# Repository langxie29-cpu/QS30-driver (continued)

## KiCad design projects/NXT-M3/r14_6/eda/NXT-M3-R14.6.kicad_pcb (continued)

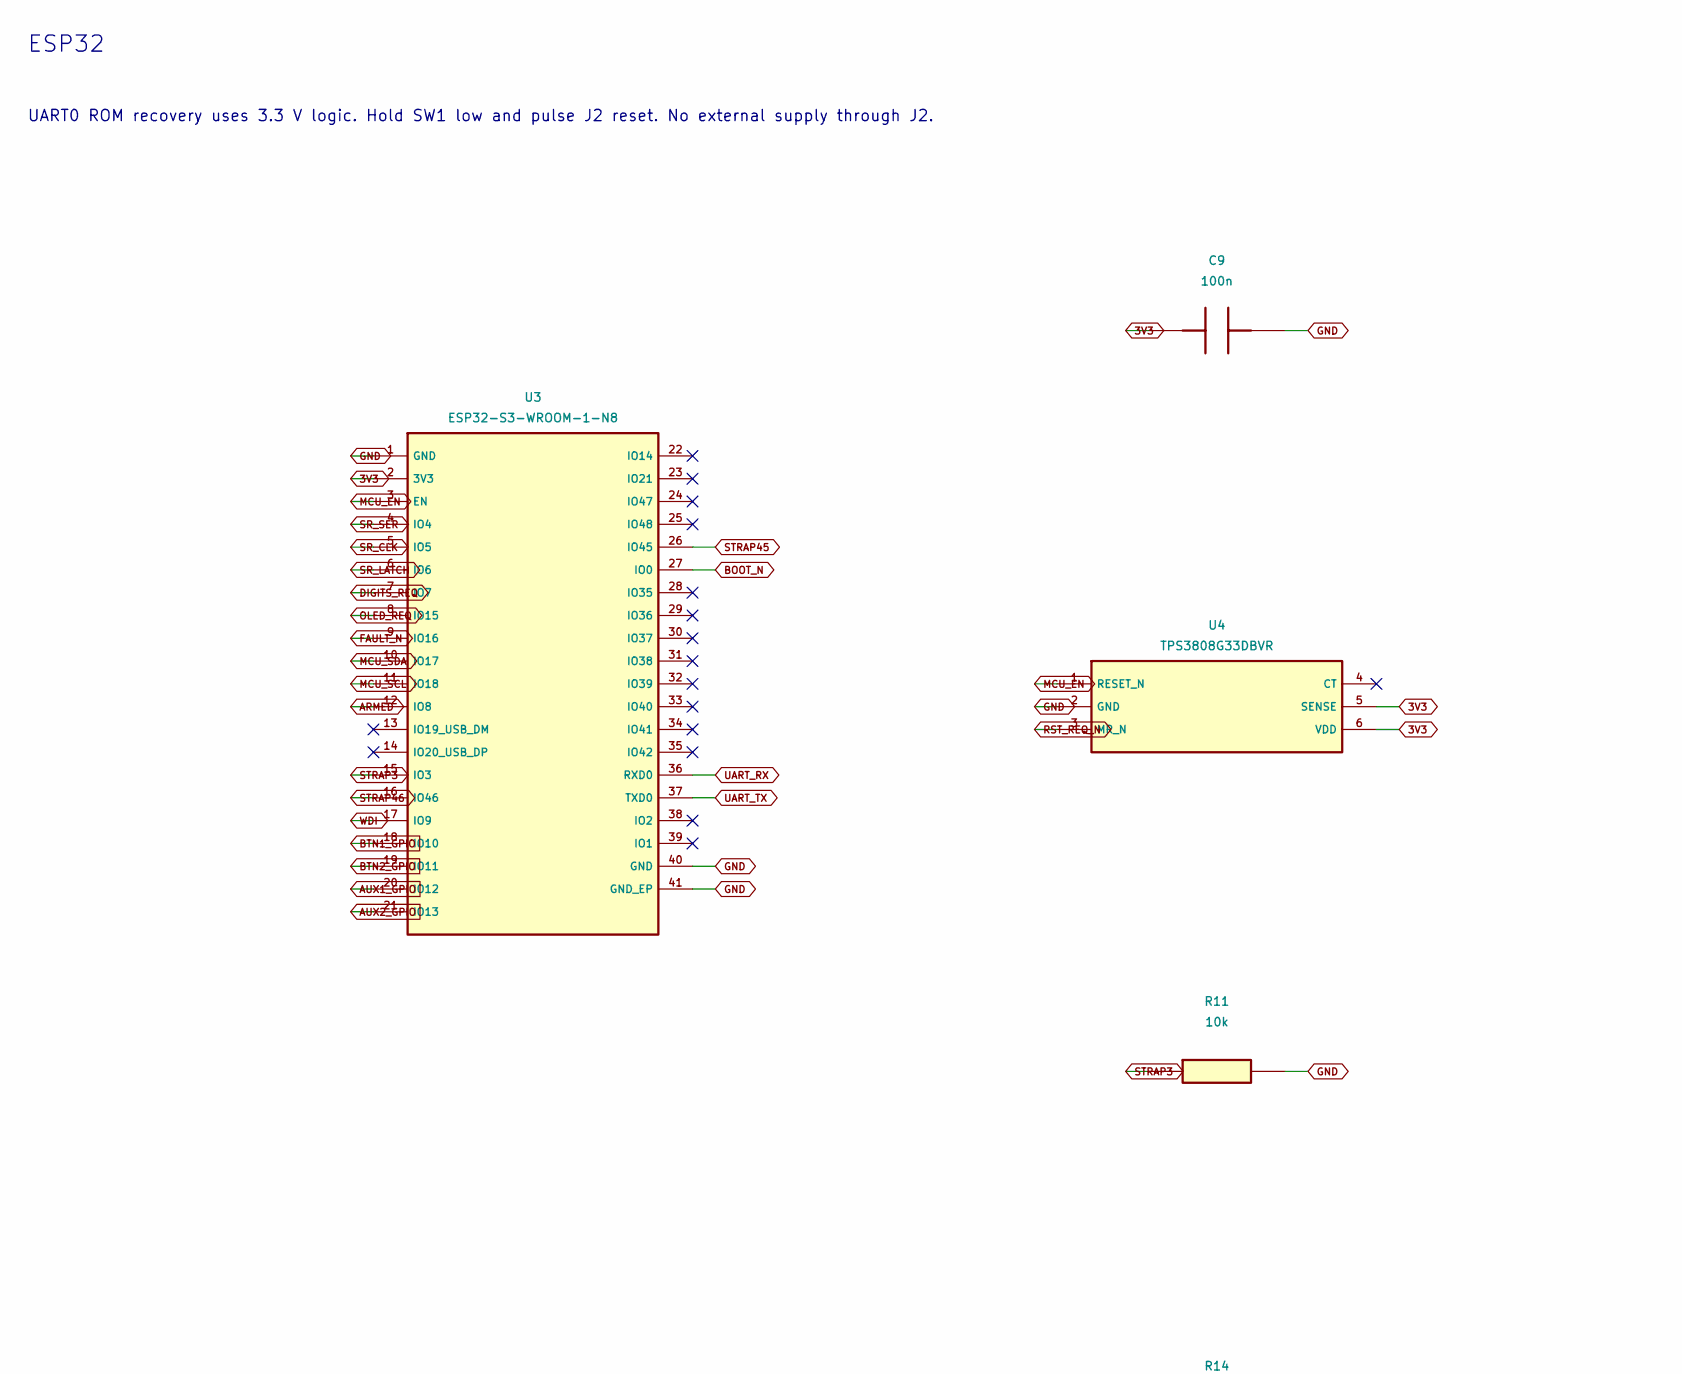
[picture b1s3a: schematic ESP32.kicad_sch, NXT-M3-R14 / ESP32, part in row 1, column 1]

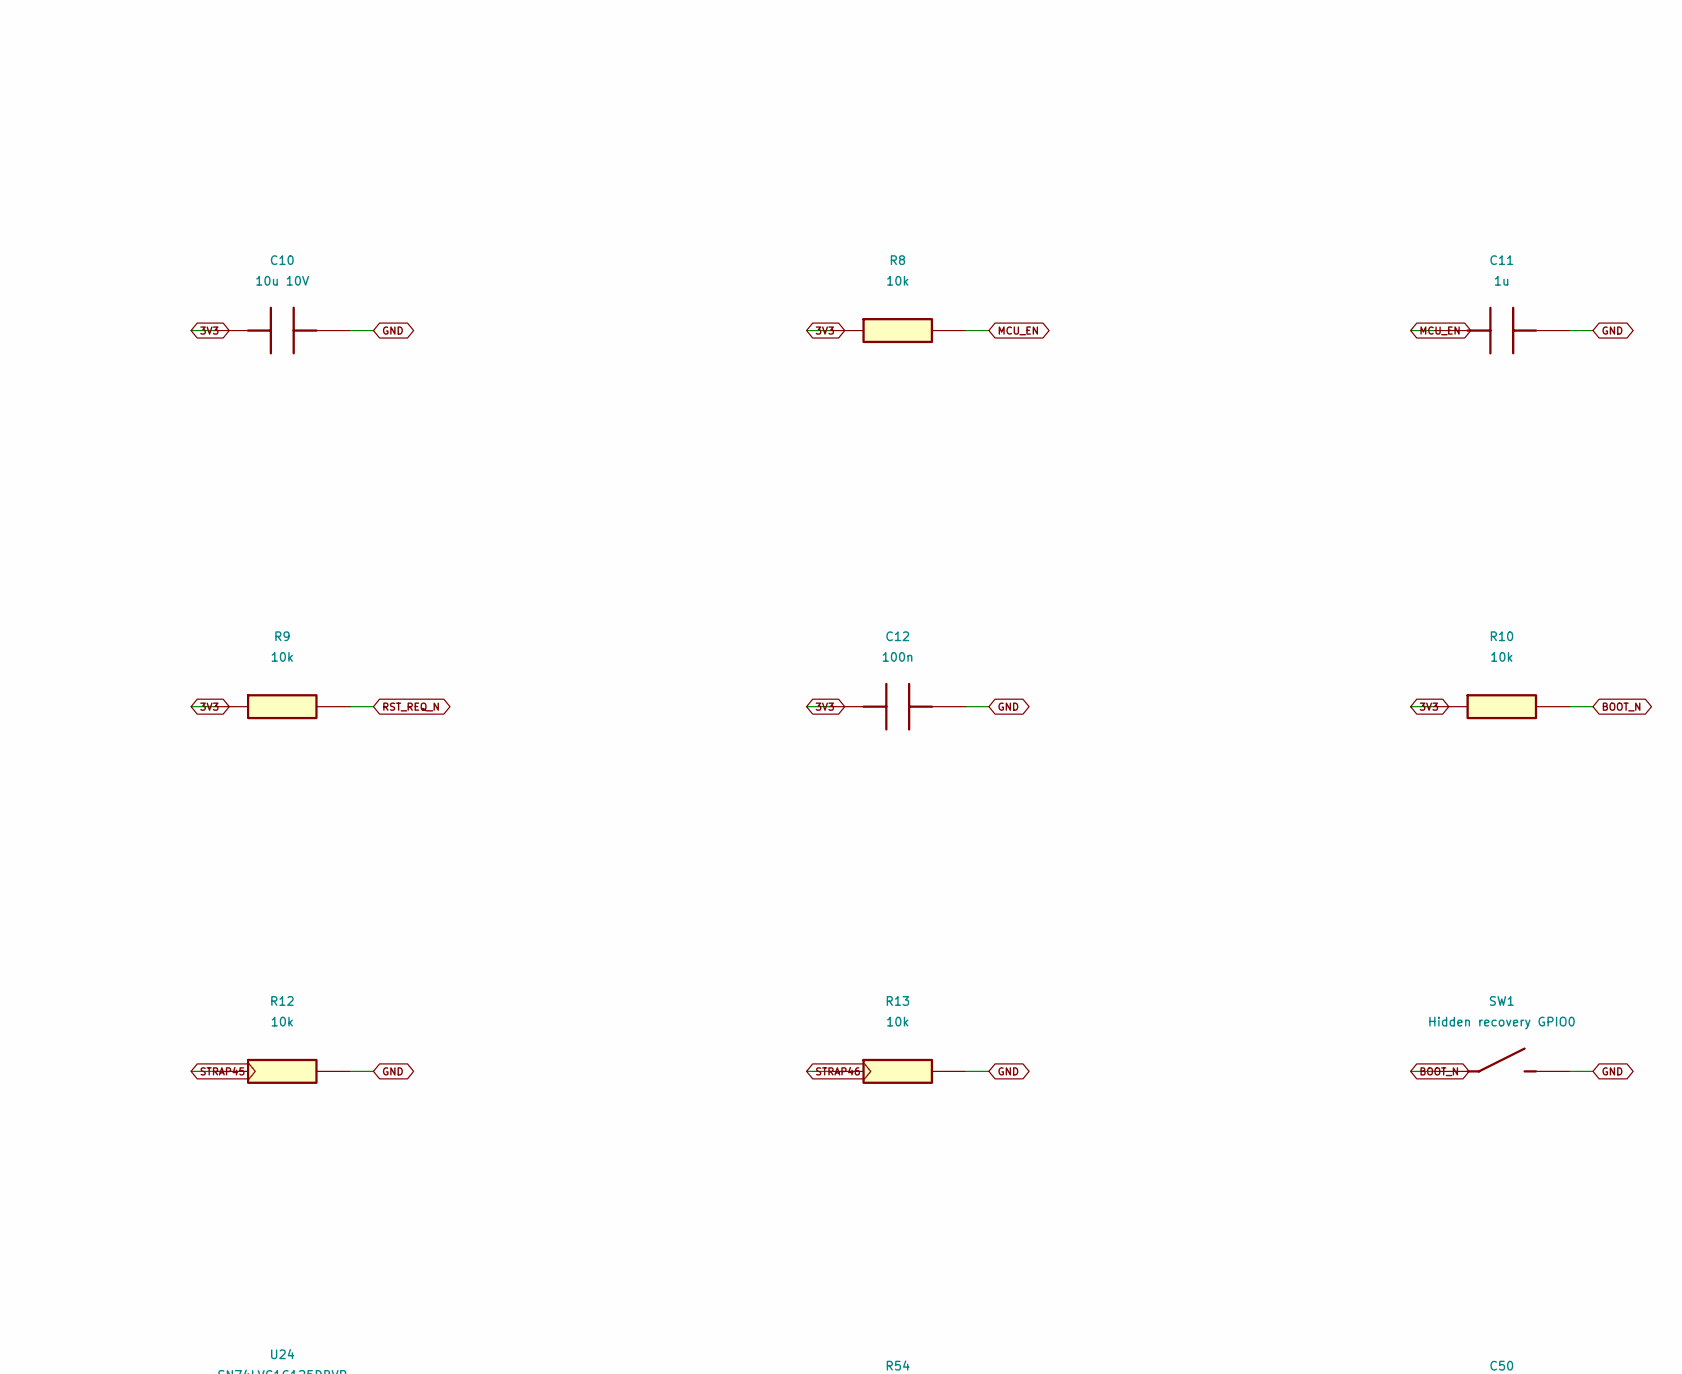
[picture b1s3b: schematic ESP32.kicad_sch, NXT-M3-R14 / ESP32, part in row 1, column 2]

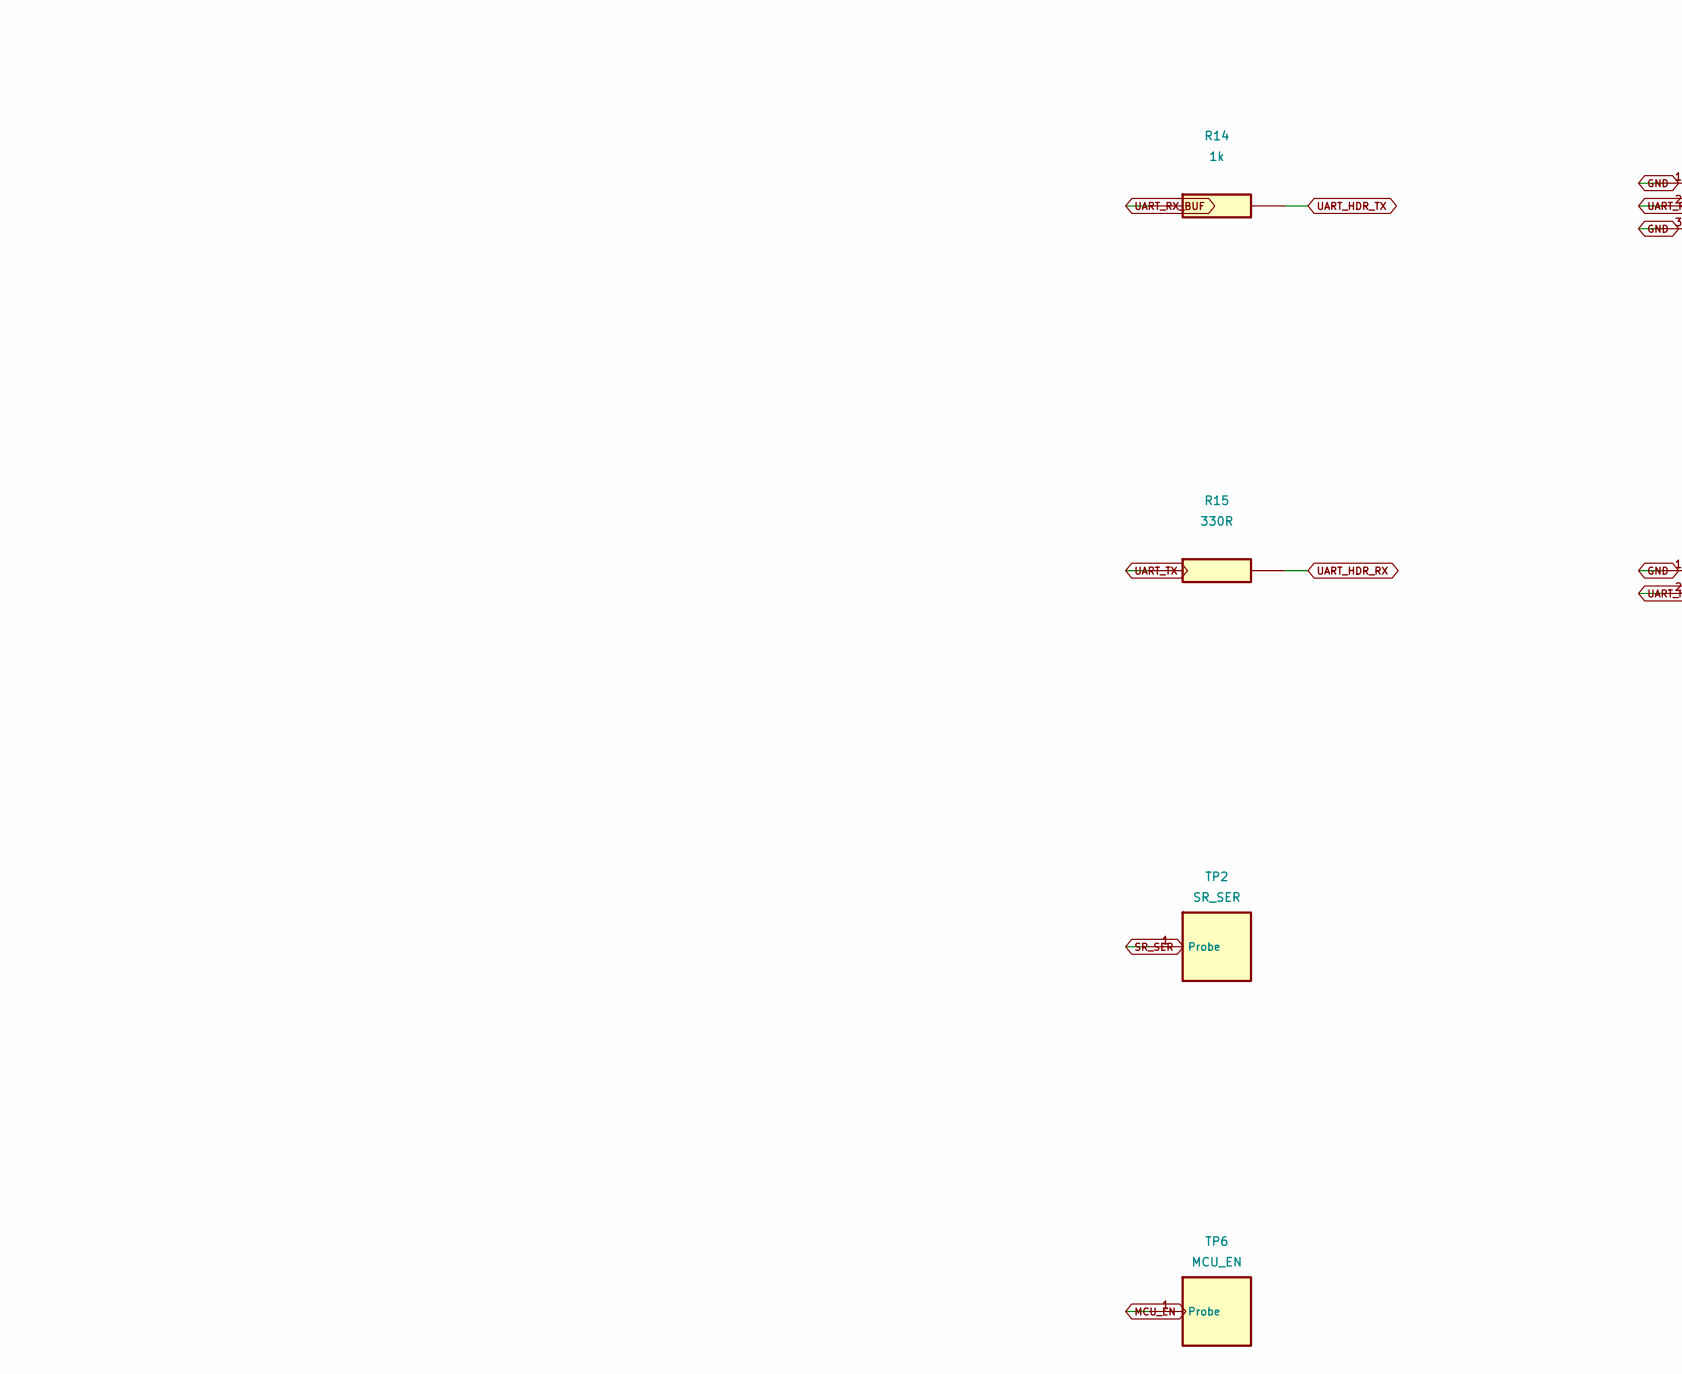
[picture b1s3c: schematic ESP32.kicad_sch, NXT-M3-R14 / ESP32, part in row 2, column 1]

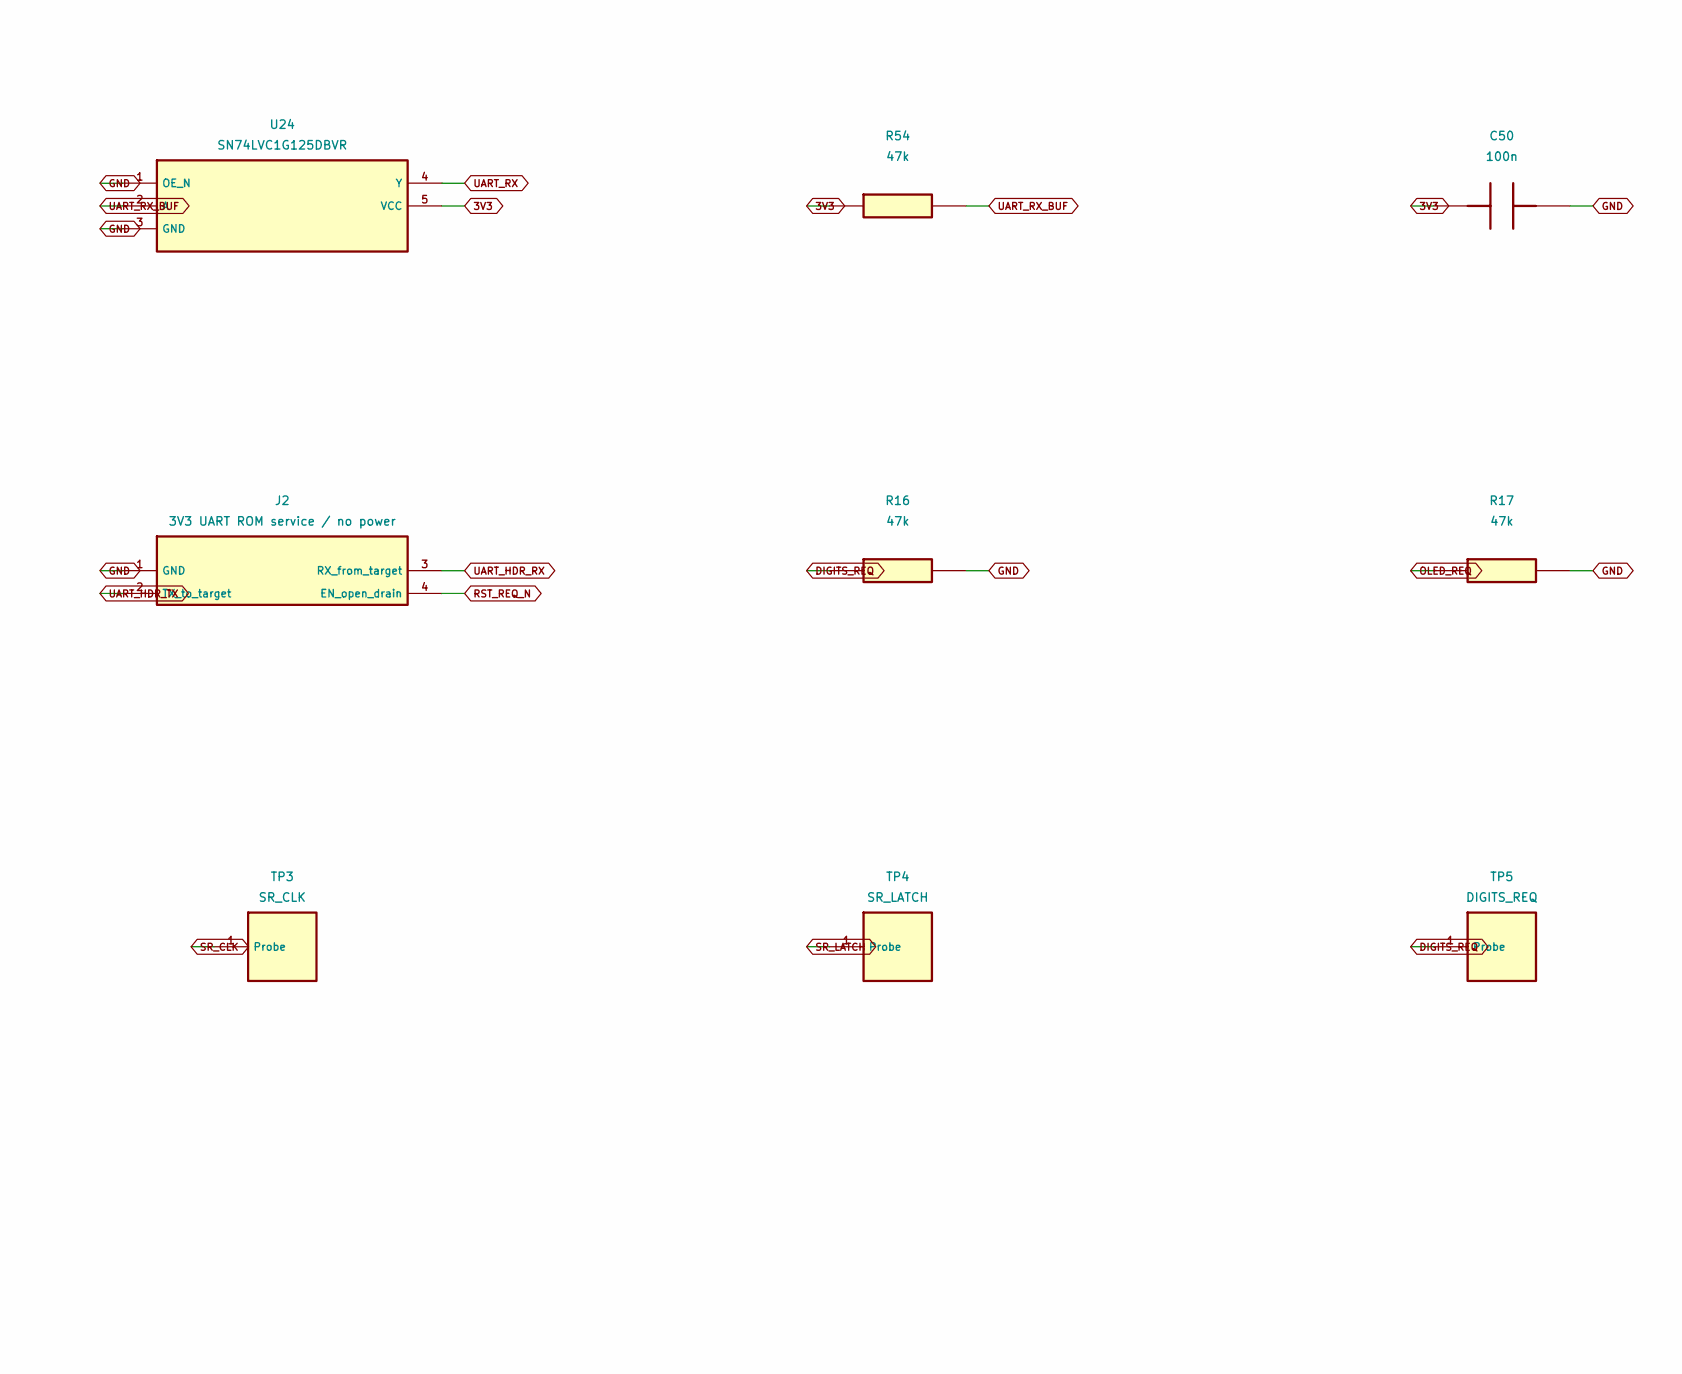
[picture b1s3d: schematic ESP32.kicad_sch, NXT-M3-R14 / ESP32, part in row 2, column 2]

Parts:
C9, C12, C50: 100n; C_0603_1608Metric
C10: 10u 10V; C_0805_2012Metric
C11: 1u; C_0603_1608Metric
J2: 3V3 UART ROM service / no power; PinHeader_1x04_P2.54mm_Vertical
R8, R9, R10, R11, R12, R13: 10k; R_0603_1608Metric
R14: 1k; R_0603_1608Metric
R15: 330R; R_0603_1608Metric
R16, R17, R54: 47k; R_0603_1608Metric
SW1: Hidden recovery GPIO0; SW_SPST_TL3342; MPN TL3342F160QG
TP2: SR_SER; TestPoint_Pad_D1.5mm
TP3: SR_CLK; TestPoint_Pad_D1.5mm
TP4: SR_LATCH; TestPoint_Pad_D1.5mm
TP5: DIGITS_REQ; TestPoint_Pad_D1.5mm
TP6: MCU_EN; TestPoint_Pad_D1.5mm
U3: ESP32-S3-WROOM-1-N8; ESP32-S3-WROOM-1_0.30mm_Drill; MPN ESP32-S3-WROOM-1-N8
U4: TPS3808G33DBVR; SOT-23-6; MPN TPS3808G33DBVR
U24: SN74LVC1G125DBVR; SOT-23-5; MPN SN74LVC1G125DBVR

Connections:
3V3: C9.1, C10.1, C12.1, C50.1, R8.1, R9.1, R10.1, R54.1, U3.2 (3V3), U4.5 (SENSE), U4.6 (VDD), U24.5 (VCC); also elsewhere on the board
ARMED: U3.12 (IO8); also elsewhere on the board
AUX1_GPIO: U3.20 (IO12); also elsewhere on the board
AUX2_GPIO: U3.21 (IO13); also elsewhere on the board
BOOT_N: R10.2, SW1.1, U3.27 (IO0)
BTN1_GPIO: U3.18 (IO10); also elsewhere on the board
BTN2_GPIO: U3.19 (IO11); also elsewhere on the board
DIGITS_REQ: R16.1, TP5.1, U3.7 (IO7); also elsewhere on the board
FAULT_N: U3.9 (IO16); also elsewhere on the board
GND: C9.2, C10.2, C11.2, C12.2, C50.2, J2.1 (GND), R11.2, R12.2, R13.2, R16.2, R17.2, SW1.2, U3.1 (GND), U3.40 (GND), U3.41 (GND_EP), U4.2 (GND), U24.1 (OE_N), U24.3 (GND); also elsewhere on the board
MCU_EN: C11.1, R8.2, TP6.1, U3.3 (EN), U4.1 (RESET_N); also elsewhere on the board
MCU_SCL: U3.11 (IO18); also elsewhere on the board
MCU_SDA: U3.10 (IO17); also elsewhere on the board
OLED_REQ: R17.1, U3.8 (IO15); also elsewhere on the board
RST_REQ_N: J2.4 (EN_open_drain), R9.2, U4.3 (MR_N)
SR_CLK: TP3.1, U3.5 (IO5); also elsewhere on the board
SR_LATCH: TP4.1, U3.6 (IO6); also elsewhere on the board
SR_SER: TP2.1, U3.4 (IO4); also elsewhere on the board
STRAP3: R11.1, U3.15 (IO3)
STRAP45: R12.1, U3.26 (IO45)
STRAP46: R13.1, U3.16 (IO46)
UART_HDR_RX: J2.3 (RX_from_target), R15.2
UART_HDR_TX: J2.2 (TX_to_target), R14.2
UART_RX: U3.36 (RXD0), U24.4 (Y)
UART_RX_BUF: R14.1, R54.2, U24.2 (A)
UART_TX: R15.1, U3.37 (TXD0)
WDI: U3.17 (IO9); also elsewhere on the board

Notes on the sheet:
ESP32
UART0 ROM recovery uses 3.3 V logic. Hold SW1 low and pulse J2 reset. No external supply through J2.

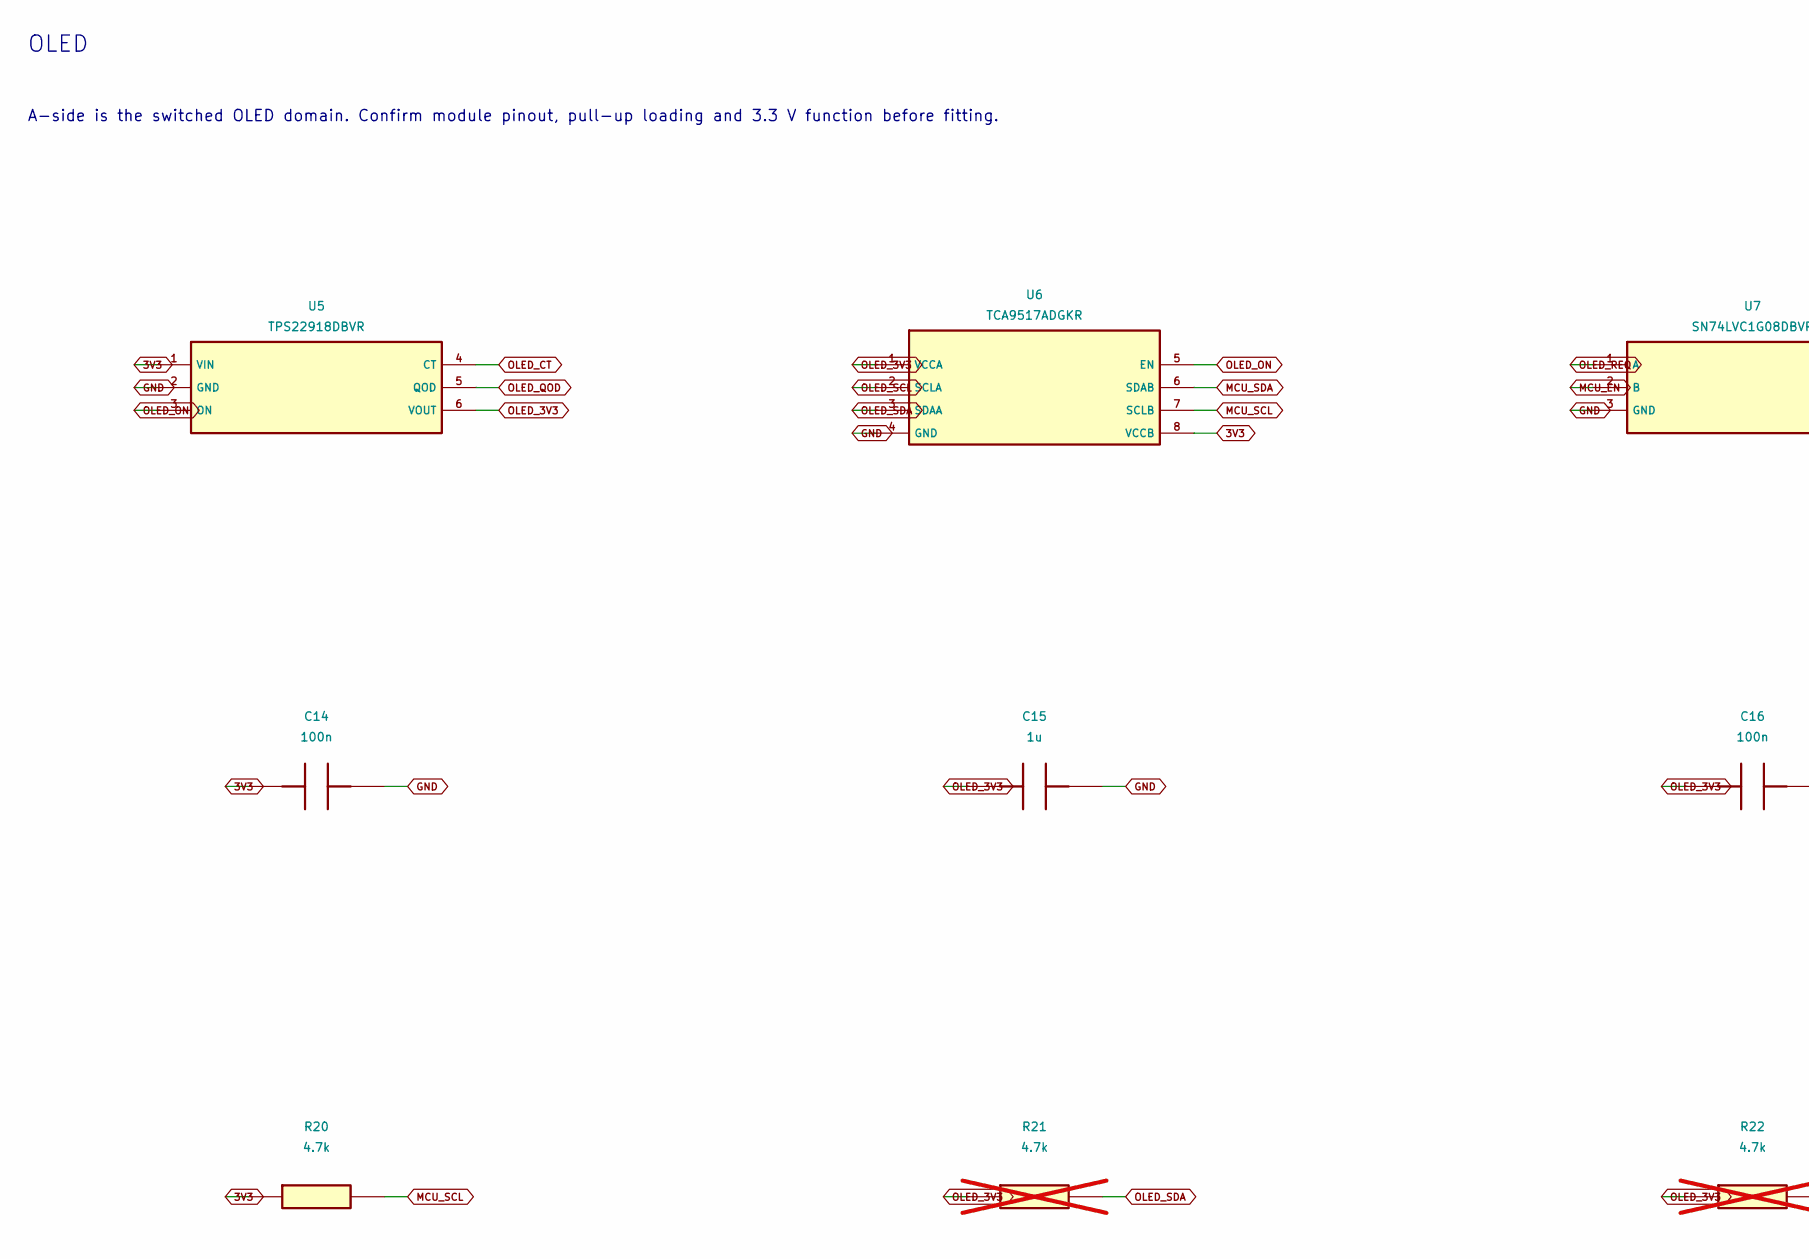
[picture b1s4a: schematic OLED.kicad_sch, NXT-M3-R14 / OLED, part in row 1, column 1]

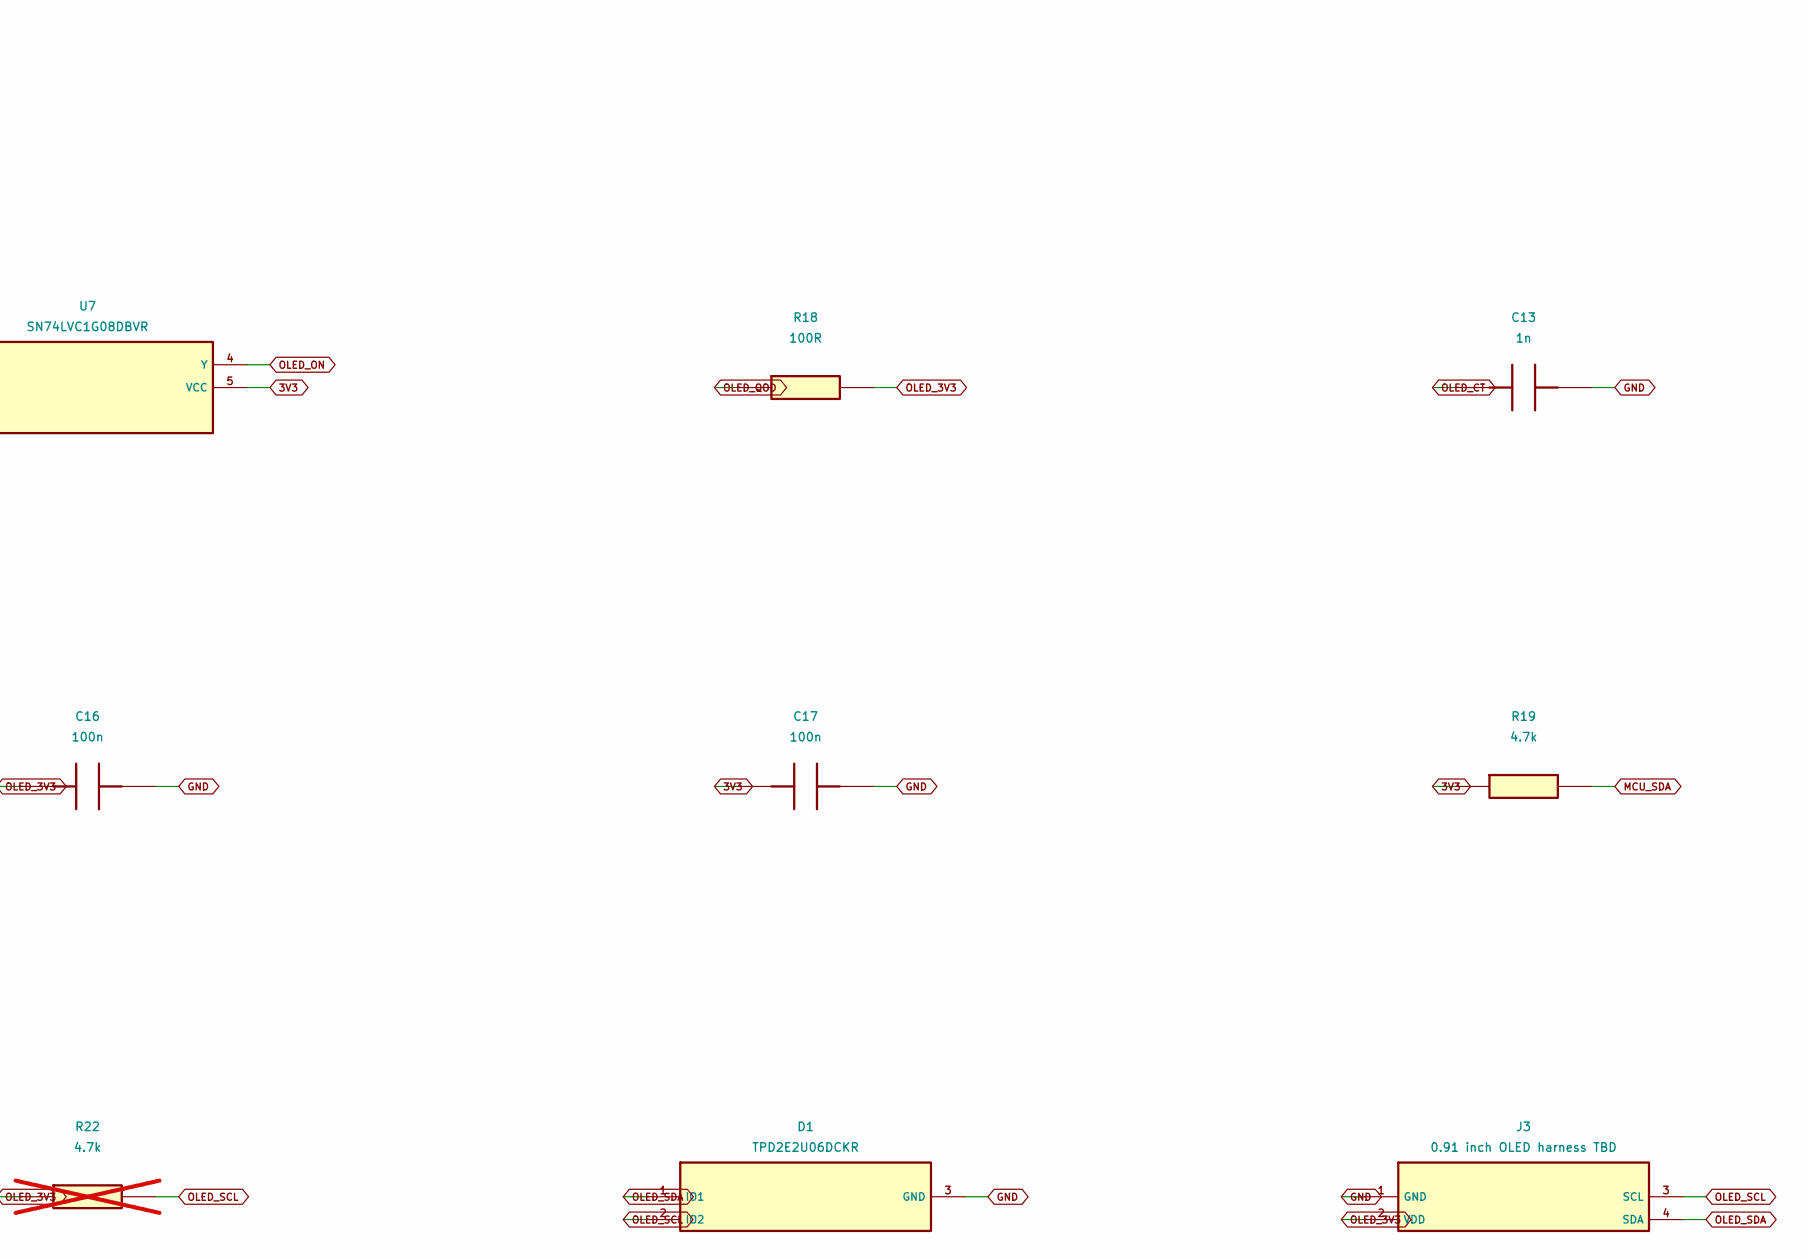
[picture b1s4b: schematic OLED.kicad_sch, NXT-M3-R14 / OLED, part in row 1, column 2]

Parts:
C13: 1n; C_0603_1608Metric
C14, C16, C17: 100n; C_0603_1608Metric
C15: 1u; C_0603_1608Metric
D1: TPD2E2U06DCKR; SOT-323_SC-70; MPN TPD2E2U06DCKR
J3: 0.91 inch OLED harness TBD; PinHeader_1x04_P2.54mm_Vertical
R18: 100R; R_0603_1608Metric
R19, R20: 4.7k; R_0603_1608Metric
R21, R22: 4.7k; R_0603_1608Metric; not fitted
U5: TPS22918DBVR; SOT-23-6; MPN TPS22918DBVR
U6: TCA9517ADGKR; TI_DGK0008A_VSSOP8; MPN TCA9517ADGKR
U7: SN74LVC1G08DBVR; SOT-23-5; MPN SN74LVC1G08DBVR

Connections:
3V3: C14.1, C17.1, R19.1, R20.1, U5.1 (VIN), U6.8 (VCCB), U7.5 (VCC); also elsewhere on the board
GND: C13.2, C14.2, C15.2, C16.2, C17.2, D1.3 (GND), J3.1 (GND), U5.2 (GND), U6.4 (GND), U7.3 (GND); also elsewhere on the board
MCU_EN: U7.2 (B); also elsewhere on the board
MCU_SCL: R20.2, U6.7 (SCLB); also elsewhere on the board
MCU_SDA: R19.2, U6.6 (SDAB); also elsewhere on the board
OLED_3V3: C15.1, C16.1, J3.2 (VDD), R18.2, R21.1, R22.1, U5.6 (VOUT), U6.1 (VCCA)
OLED_CT: C13.1, U5.4 (CT)
OLED_ON: U5.3 (ON), U6.5 (EN), U7.4 (Y)
OLED_QOD: R18.1, U5.5 (QOD)
OLED_REQ: U7.1 (A); also elsewhere on the board
OLED_SCL: D1.2 (IO2), J3.3 (SCL), R22.2, U6.2 (SCLA)
OLED_SDA: D1.1 (IO1), J3.4 (SDA), R21.2, U6.3 (SDAA)

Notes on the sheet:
OLED
A-side is the switched OLED domain. Confirm module pinout, pull-up loading and 3.3 V function before fitting.

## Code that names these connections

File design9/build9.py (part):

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        add(ref, val, "C", val, "1206" if ref == "C1" else "0603", S)
        d.conn(ref, 1, "EXT12"); d.conn(ref, 2, "GND")
    add("U5", "TPS54202DDCR", "TPS54202", "12 V→5.08 V 2 A", "SOT-23-6", S, "VERIFIED")
    for pin, net in (("1", "GND"), ("2", "EXT5_SW"), ("3", "EXT12"), ("4", "EXT5_FB"),
                     ("5", "EXT12"), ("6", "EXT5_BOOT")):
        d.conn("U5", pin, net)
    add("C4", "100nF", "C", "BOOT 电容", "0603", S, "VERIFIED")
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        add(ref, "5.1k", "R", "5.1 kΩ CC 下拉", "0603", S, "VERIFIED")
        d.conn(ref, 1, net); d.conn(ref, 2, "GND")
    add("U2", "USBLC6-2SC6", "USBLC6-2SC6", "USB ESD 保护", "SOT-23-6", S, "VERIFIED")
    for pin, net in (("1", "USB_DP"), ("2", "GND"), ("3", "USB_DM"), ("4", "USB_DM_MCU"),
                     ("5", "VBUS"), ("6", "USB_DP_MCU")):
        d.conn("U2", pin, net)
    add("D2", "SS14", "D", "40 V 1 A", "SMA", S, "VERIFIED")
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    mcu = {"1": "GND", "2": "3V3", "3": "EN_MCU", "4": "KEY_SET", "5": "KEY_PLUS",
           "6": "KEY_MINUS", "7": "HVF_NODE", "8": "DISP_ALLOW", "9": "HV_EN_REQ",
           "10": "STATUS_LED", "11": "OVP_RST", "12": "I2C_SDA", "13": "USB_DM_MCU",
           "14": "USB_DP_MCU", "16": "GPIO46_STRAP", "17": "I2C_SCL", "19": "DISP_DIN",
           "20": "DISP_CLK", "22": "DISP_LAT", "27": "BOOT_N", "36": "UART0_RX",
           "37": "UART0_TX", "39": "HV_SENSE_ADC", "40": "GND", "41": "GND"}
    for pin, net in mcu.items():
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    add("LED1", "LED", "LED", "状态灯", "0603", S, "VERIFIED")
    d.conn("LED1", 1, "LED_A"); d.conn("LED1", 2, "STATUS_LED")
    add("R46S", "10k", "R", "GPIO46 strap 下拉", "0603", S, "VERIFIED")
    d.conn("R46S", 1, "GPIO46_STRAP"); d.conn("R46S", 2, "GND")
    add("J3", "HDR-6", "HDR-6", "I2C/扩展排针", "HDR-6", S, "PROVISIONAL")
    for pin, net in (("1", "3V3"), ("2", "GND"), ("3", "I2C_SCL"), ("4", "I2C_SDA"),
                     ("5", "GND"), ("6", "GND")):
        d.conn("J3", pin, net)
    add("J4", "HDR-6", "HDR-6", "UART0 恢复排针", "HDR-6", S, "PROVISIONAL")
    for pin, net in (("1", "GND"), ("2", "3V3"), ("3", "UART0_TX"), ("4", "UART0_RX"),
                     ("5", "GND"), ("6", "GND")):
        d.conn("J4", pin, net)

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    add("C8", "100nF", "C", "基准滤波", "0603", S, "VERIFIED")
    d.conn("C8", 1, "VREF_1V0"); d.conn("C8", 2, "GND")
    add("U8", "LM393DR", "LM393", "DRV_PG + FAULT_OK（3.3 V 供电/1.0 V 基准）", "SOIC-8", S, "VERIFIED")
    for pin, net in (("1", "DRV_PG"), ("2", "VREF_1V0"), ("3", "DRV_SNS"), ("4", "GND"),
                     ("5", "HVF_NODE"), ("6", "VREF_1V0"), ("7", "FAULT_OK"), ("8", "3V3")):
        d.conn("U8", pin, net)
    add("R20", "102k", "R", "DRV_SNS 上（1%）", "0603", S, "VERIFIED")
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    add("R24", "10k", "R", "FAULT_OK 上拉", "0603", S, "VERIFIED")
    d.conn("R24", 1, "FAULT_OK"); d.conn("R24", 2, "3V3")
    add("U11", "LM393DR", "LM393", "EXT12_PG/P3V3_PG（1.0 V 基准）", "SOIC-8", S, "VERIFIED")
    for pin, net in (("1", "EXT12_PG"), ("2", "VREF_1V0"), ("3", "EXT12_SNS"), ("4", "GND"),
                     ("5", "P3V3_SNS"), ("6", "VREF_1V0"), ("7", "P3V3_PG"), ("8", "3V3")):
        d.conn("U11", pin, net)
    add("R25", "100k", "R", "EXT12_SNS 上（→10.5 V 触发）", "0603", S, "VERIFIED")
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    # ---------------- 升压 + OVP ----------------
    S = "MB_HV"
    add("U20", "UC3843AN", "UC3843", "电流型 PWM", "DIP-8", S, "VERIFIED")
    for pin, net in (("1", "COMP_N"), ("2", "FB_HV"), ("3", "CS_FILT"), ("4", "RT_CT"),
                     ("5", "GND"), ("6", "HV_GATE"), ("7", "HV_IN"), ("8", "VREF_UC")):
        d.conn("U20", pin, net)
    add("U21", "TL431", "TL431", "UC3843 VREF 2.5 V", "SOT-23", S, "VERIFIED")
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    add("C16", "100nF", "C", "OVP 滤波", "0603", S, "VERIFIED")
    d.conn("C16", 1, "OVP_SNS"); d.conn("C16", 2, "GND")
    add("U23", "LM393DR", "LM393", "OVP 比较器（EXT12 供电）", "SOIC-8", S, "VERIFIED")
    for pin, net in (("1", "OVP_SET"), ("2", "VREF_OVP"), ("3", "OVP_SNS"), ("4", "GND"),
                     ("5", "GND"), ("6", "VREF_OVP"), ("8", "EXT12")):
        d.conn("U23", pin, net)
    d.nc.append(("U23", "7"))
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            d.conn("R_SAFE_C", 1, "SAFETY_LOOP_C_IN"); d.conn("R_SAFE_C", 2, "SAFETY_LOOP_C_OUT")
        else:
            add(f"J_MOD_{m}_LV", "2x8-IDC-2.54-keyed", "CONN-LV-16", f"{name} 低压接口", "IDC-16", S)
            for pin, net in (("1", "3V3"), ("2", "GND"), ("3", "DRV_VDD"), ("4", "GND"),
                             ("5", f"MOD_{m}_DIN"), ("6", f"MOD_{m}_DOUT"),
                             ("7", "DISP_CLK"), ("8", "DISP_LAT"), ("9", "DISP_ALLOW"),
                             ("10", f"SAFETY_LOOP_{m}_IN"), ("11", f"SAFETY_LOOP_{m}_OUT"),
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            d.conn(f"R_SAFE_{m}", 1, f"SAFETY_LOOP_{m}_IN")
            d.conn(f"R_SAFE_{m}", 2, f"SAFETY_LOOP_{m}_OUT")
            add(f"J_MAIN_{m}_LV", "2x8-IDC-2.54-keyed", "CONN-LV-16", f"{name} 低压插座", "IDC-16", "MB_CONN", S)
            for pin, net in (("1", "3V3"), ("2", "GND"), ("3", "DRV_VDD"), ("4", "GND"),
                             ("5", f"MOD_{m}_DIN"), ("6", f"MOD_{m}_DOUT"),
                             ("7", "DISP_CLK"), ("8", "DISP_LAT"), ("9", "DISP_ALLOW"),
                             ("10", f"SAFETY_LOOP_{m}_IN"), ("11", f"SAFETY_LOOP_{m}_OUT"),
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        down = f"U_DS_{m}"
        add(down, "CD40109BNSR", "CD40109B", "12→3.3 V DOUT", "SOP-16-NS", S,
            "PROVISIONAL", "TI SCHS099B p1 permits VCC>VDD; timing/power-loss validation pending")
        for pin, net in {1: "DRV_VDD", 16: "3V3", 8: "GND", 2: "DRV_VDD",
                         3: f"{dev}_DOUT", 4: f"MOD_{m}_DOUT",
                         6: "GND", 7: "GND", 9: "GND", 10: "GND", 14: "GND", 15: "GND"}.items():
            d.conn(down, pin, net)
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    # 数据链
    chk("E11", by_net.get("MOD_L_DOUT") and any(r == "J_MAIN_L_LV" for r, _ in by_net["MOD_L_DOUT"]),
        "L 模块 DATA OUT 回到主板（回线）")
    chk("E12", by_net.get("MOD_C_DIN") and len(by_net["MOD_C_DIN"]) >= 1,
        "中心模块 DATA IN 接 L 模块回线")
    chk("E13", by_net.get("MOD_R_DIN") and any(r == "J_MAIN_R_LV" for r, _ in by_net["MOD_R_DIN"]),
        "R 模块 DATA IN 经连接器")
    chk("E14", by_net.get("DISP_CLK") and len(by_net["DISP_CLK"]) >= 4,
        "CLK 并行分配到 3 模块（含主板）")
    chk("E15", by_net.get("DISP_ALLOW") and len(by_net["DISP_ALLOW"]) >= 4, "BL/ALLOW 并行分配")
    # 安全回路
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        (15, "GND", "逻辑地", ""),
        (16, "GND", "逻辑地", ""),
    ]
    hv = [(1, "HV_BUS", "172 V DC（危险）", "≥300 V 额定连接器，防触碰，Pin1 标识"),
          (2, "GND_HV", "高压回流（单点接 GND）", "独立线束")]
    return pins, hv

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
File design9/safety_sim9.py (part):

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                  f'C{u}_PAR {node} 0 100p']
    # LM393: open collector, 50-ohm saturated sink approximation; 1 us pole.
    def comparator(label,out,minus,plus):
        supply = 'EXT12' if label=='OVP' else '3V3'
        lines.extend([f'B{label}_DIFF {label}_raw 0 V=v({plus})-v({minus})',
                      f'R{label}_DELAY {label}_raw {label}_ctl 1k',
                      f'C{label}_DELAY {label}_ctl 0 1n',
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            record['metrics']=metrics
            record['protection_signoff']='FAIL' # Known unresolved CS/latch topology; no all-corner qualification.
            fig,axs=plt.subplots(3,1,figsize=(10,8),sharex=True)
            for name in ['v(HV_BUS)','v(HV_IN)','v(DRV_VDD)']:axs[0].plot(t*1e3,v(name),label=name)
            for name in ['v(OVP_SNS)','v(VREF_OVP)','v(OVP_SET)','v(OVP_LATCH)','v(COMP_N)']:axs[1].plot(t*1e3,v(name),label=name)
            for name in ['@Q21[ic]','@Q22[ic]','@Q25[ic]','i(L20)']:axs[2].plot(t*1e3,v(name),label=name)
            for ax in axs:ax.legend(fontsize=7);ax.grid();ax.set_ylabel('V' if ax!=axs[2] else 'A')
            axs[2].set_xlabel('time (ms)');fig.suptitle(f'{run_name}: {case["id"]} — diagnostic equivalent, NOT signoff')
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
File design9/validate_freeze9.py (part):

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                  (f'U_DS_{m}','3'):f'U_{m}_DOUT',(f'U_DS_{m}','4'):f'MOD_{m}_DOUT',
                  (f'U_DS_{m}','1'):'DRV_VDD',(f'U_DS_{m}','16'):'3V3',
                  (f'U_{m}','27'):'DRV_VDD',(f'U_{m}','29'):'GND',(f'U_{m}','30'):'DRV_VDD'}
        for logic_pin, ls_pin, hv_pin, global_net in [('CLK','5','28','DISP_CLK'),('LAT','11','31','DISP_LAT'),('BL','13','33','DISP_ALLOW')]:
            wanted[(f'U_{m}',hv_pin)] = f'U_{m}_{logic_pin}'
            wanted[(f'U_LS_{m}',ls_pin)] = f'U_{m}_{logic_pin}'
            wanted[(f'U_LS_{m}',{'CLK':'6','LAT':'10','BL':'14'}[logic_pin])] = global_net
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
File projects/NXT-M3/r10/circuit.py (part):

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r("R10","10k",V,"BOOT_N")
for idx, strap in enumerate(("STRAP3","STRAP45","STRAP46"),11):
    r(f"R{idx}","10k",strap,G)
add("SW1","Switch","Hidden recovery GPIO0","BOOT_N GND","TL3342F160QG")
r("R14","1k","UART_RX_BUF","UART_HDR_TX")
add("U24","UARTBuffer","SN74LVC1G125DBVR","GND UART_RX_BUF GND UART_RX 3V3","SN74LVC1G125DBVR")
r("R54","47k",V,"UART_RX_BUF")
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    ("8",12,"ARMED","IN","Hardware latch state"),
    ("9",17,"WDI","OUT","Watchdog candidate falling edge every 1.1 s, no hardware PWM"),
    ("3",15,"STRAP3","STRAP","10k low, ROM JTAG policy verify"),
    ("46",16,"STRAP46","STRAP","10k low for UART download with GPIO0 low"),
    ("45",26,"STRAP45","STRAP","10k low for default flash supply"),
    ("0",27,"BOOT_N","STRAP","10k high, hold SW1 while asserting J2 EN"),
    ("44",36,"UART_RX","IN","Use 3.3V UART only, no adapter power pin"),
    ("43",37,"UART_TX","OUT","ROM serial recovery"),
    ("EN",3,"MCU_EN","RESET","TPS3808 supervisor, pull-up and C11"),
]
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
